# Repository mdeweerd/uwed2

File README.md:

# WARNING

Project not tested.

# INFORMATION

This is based on the open-source project "Open-Source Potentiostat
for Wireless Electrochemical Detection with Smartphones" 
=
See : https://dash.harvard.edu/bitstream/handle/1/37298552/5997382.pdf;jsessionid=20A09C47E57A66C76ECFA98192F31BF9?sequence=1

The reference to "UWED, Alar Ainla, GMW Group Harvard Univ" was left on the PCB.  They did not design this one, but it was adapted from their Eagle Project.

- The wireless module was replaced with an ESP-WROOM-32 because the original module is no longer supported.
- A programming connector was added.
- A THT connector has been added for power.
- A "Battery Management" IC was added to safely charge a Li-Ion/Li-Poly on power connector.
- There was a project to ajust the PAD positions to a Molex/1719730004

And some other "minor" changes as well as an effort to improve the ground plaine.

# SOFTWARE

See ac8b00850_si_002.zip from https://www.ncbi.nlm.nih.gov/pmc/articles/PMC5997382/ to get the original software as well as further information about this project.

The software has to be adapted to the ESP-WROOM-32.

# BUYING COMPONENTS

The original project ensured that all components were available from Digikey.

The `UWED2_proto.xls` file shows where these components were available in 2019.

At that time you would have been able to paste the following list on https://www.digikey.com/ordering/shoppingcart, but the BOM needs to be updated for some passive components and the ESP-WROOM-32 (was: 1904-1010-1-ND):
```csv
2,401-1427-1-ND,BOOT1;EN1
6,490-3340-2-ND,C1;C2;C5;C6;C16;C18
2,311-1136-1-ND,C10;C12
2,399-16641-1-ND,C20;C21
2,1276-1300-1-ND,C3;C4
9,478-1395-1-ND,C7-C9;C11;C13-C15;C17;C19
1,497-18870-1-ND,D7
1,1904-1010-1-ND,IC1
1,AD5667RBRMZ-2-ND,IC2
1,AD8608ARUZ-ND,IC3
2,576-1259-1-ND,IC4;IC5
1,MAX4643EUA+-ND,IC6
1,MAX4644EUT+TCT-ND,IC7
1,LTC2471IMS#PBF-ND,IC8
1,VAOL-S8SB4CT-ND,LED1
1,CP-032HPJCT-ND,P1
1,GH7540CT-ND,P2
1,RR12P1.2KDCT-ND,R1
2,541-4163-1-ND,R11;R12
2,A130132CT-ND,R14;R15
1,311-16.2KCRCT-ND,R2
2,311-845CRCT-ND,R3;R10
1,311-29.4KCRCT-ND,R4
1,311-8.06KCRCT-ND,R5
1,541-4126-1-ND,R7
3,541-4164-1-ND,R8;R9;R13
```

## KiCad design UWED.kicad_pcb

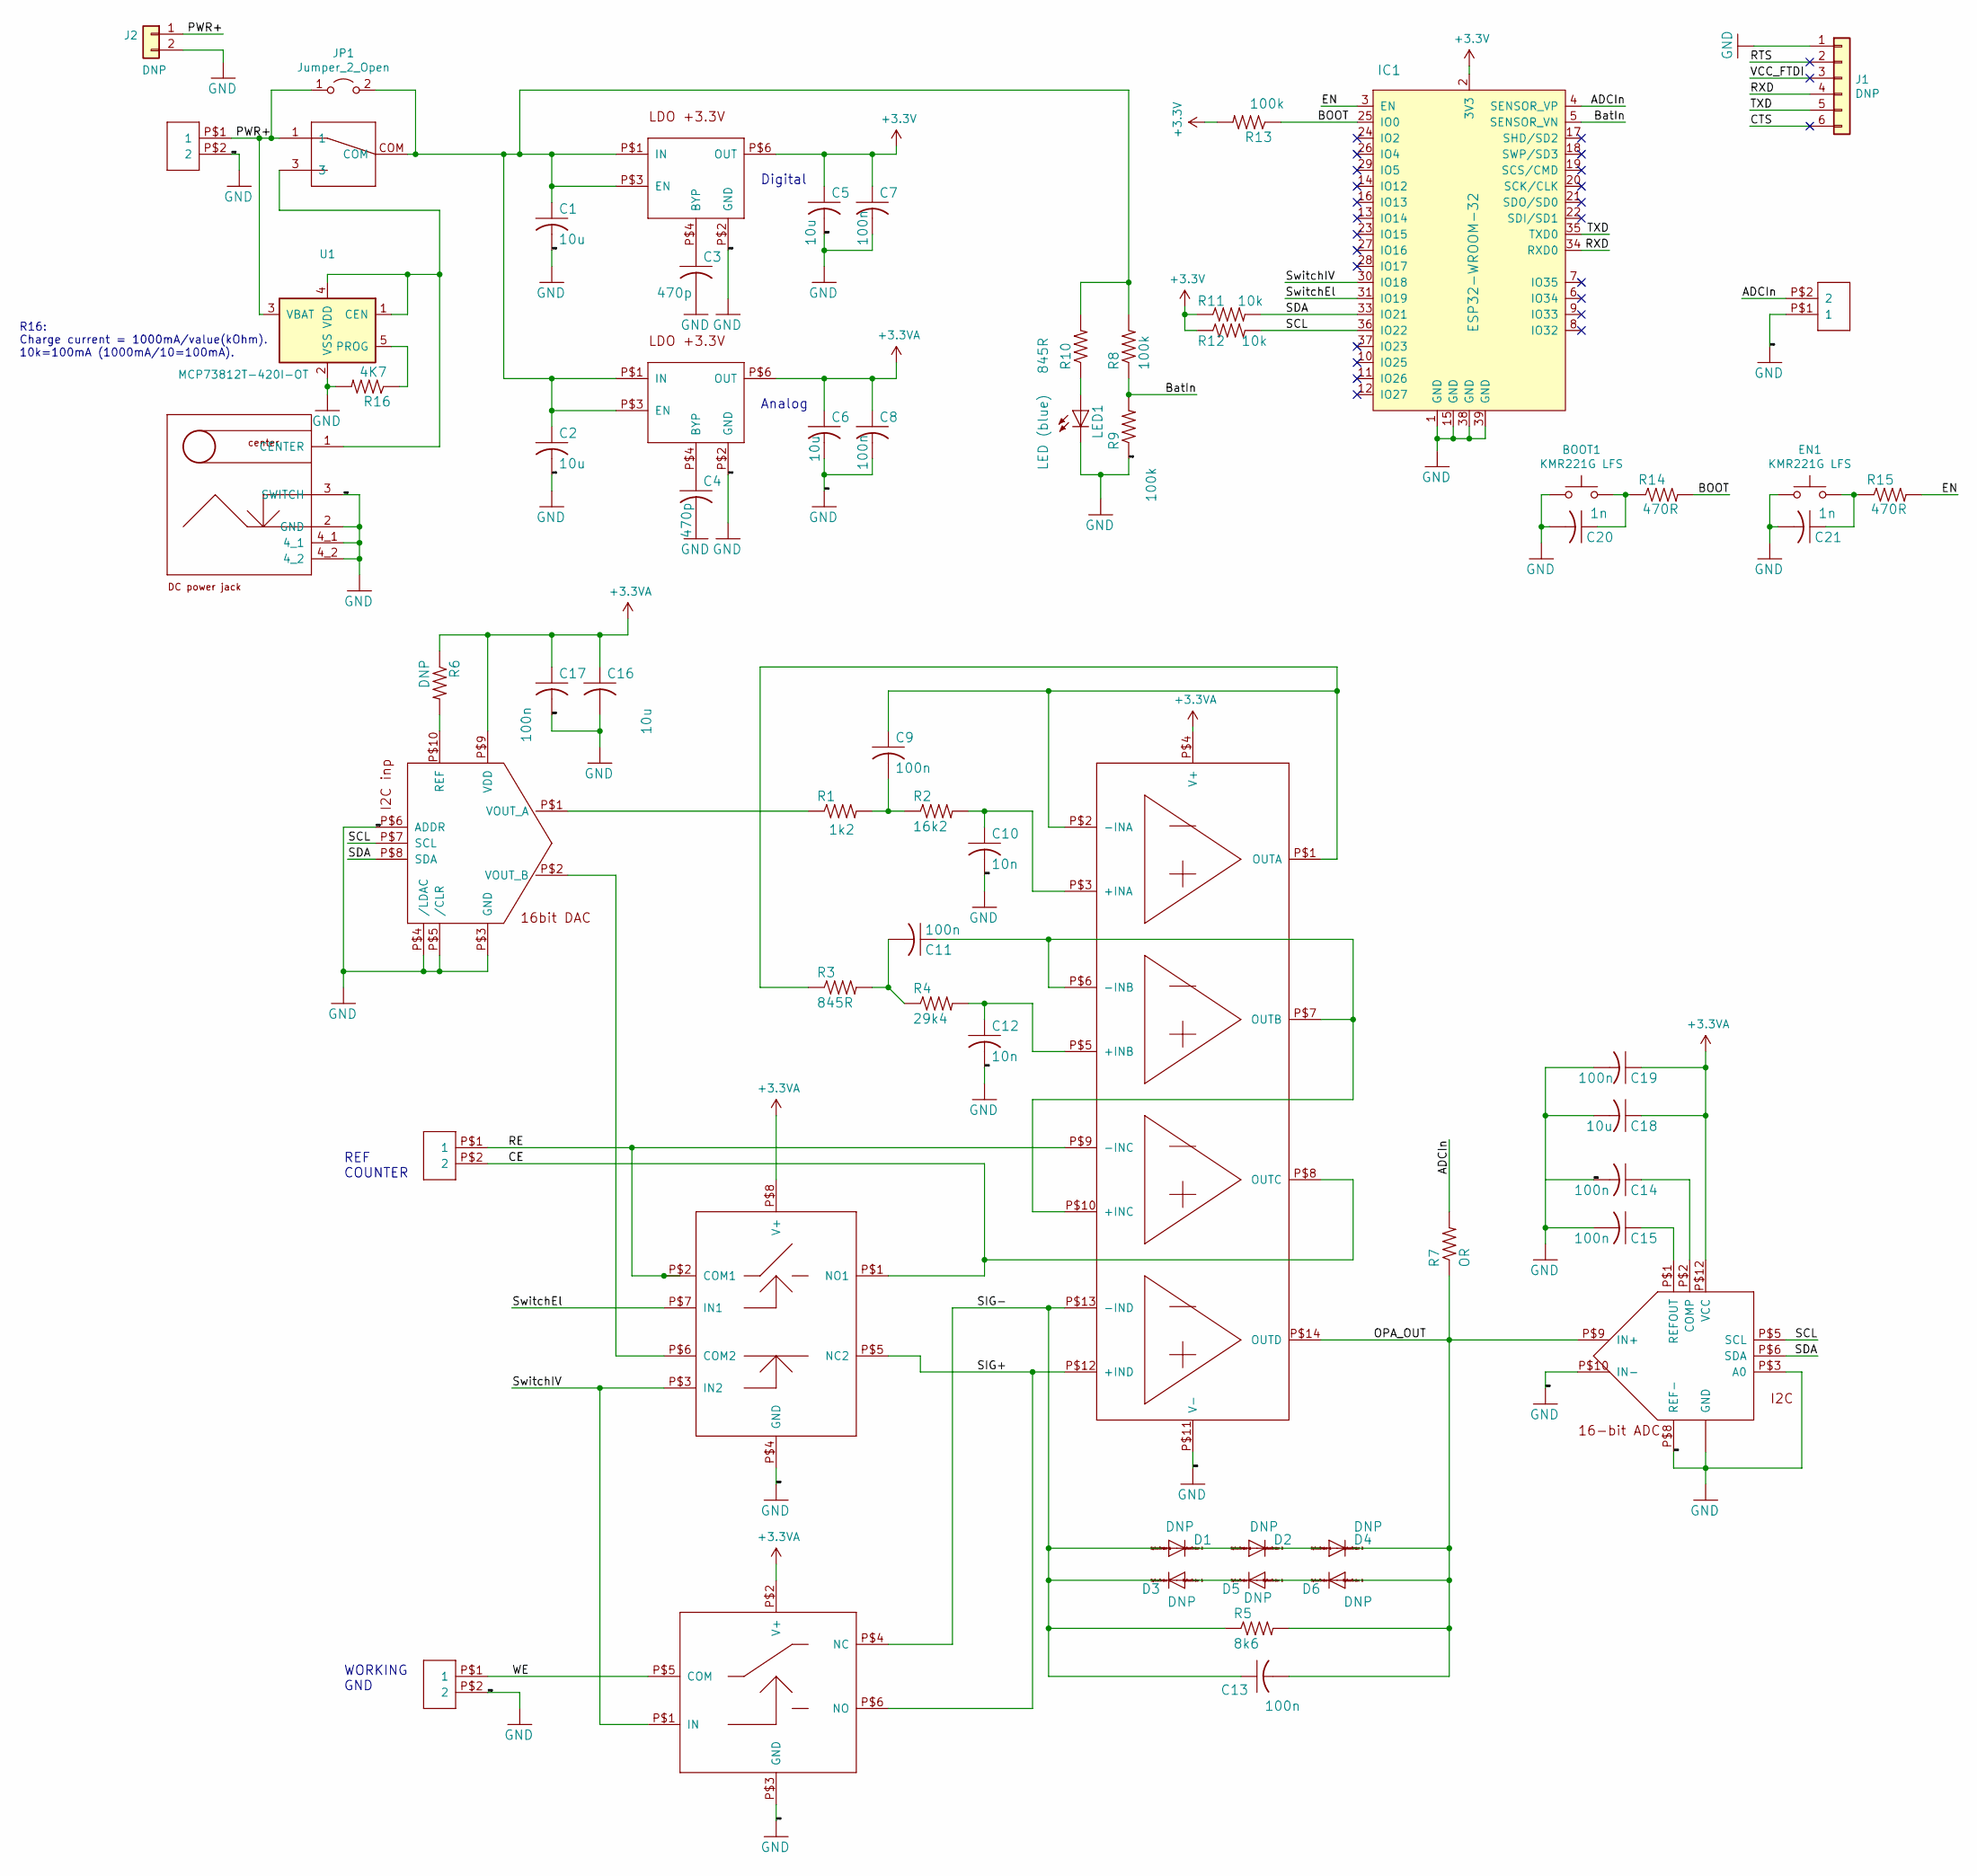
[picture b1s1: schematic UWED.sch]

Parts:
BOOT1: KMR221G LFS; SW_SPST_KMR2; mouser.manf# 611-KMR221G-LFS
C1, C2, C5, C6, C16, C18: 10u; C0805; digikey.manf# 490-3340-1-ND
C3, C4: 470p; C0805; digikey.manf# 1276-1300-1-ND
C7, C8, C9, C11, C13, C14, C15, C17, C19: 100n; C0805; digikey.manf# 478-1395-1-ND
C10, C12: 10n; C0805; digikey.manf# 311-1136-1-ND
C20, C21: 1n; C0805; digikey.manf# 399-16641-1-ND
D1, D2, D3, D4, D5, D6: DNP; SOD80C
EN1: KMR221G LFS; SW_SPST_KMR2; mouser.manf# 611-KMR221G-LFS
IC1: ESP32-WROOM-32; ESP32-WROOM-32D; MPN ESP32-WROOM-32; digikey.manf# 1904-1010-1-ND
IC2: DAC_AD5667RBRMZ-2; MSOP10_0.5MM; MPN AD5667RBRMZ-2; digikey.manf# AD5667RBRMZ-2-ND
IC3: 4OPAMPS-AD8608ARUZ; MSOP14_0.65MM; MPN AD8608ARUZ; digikey.manf# AD868ARUZ-ND
IC4, IC5: LDO-MIC5205-3.3YM5-TR; SOT-23-6; MPN MIC5205-3.3YM5-TR; digikey.manf# 576-1259-1-ND
IC6: SWITCH_MAX4643EUA; MSOP8_0.65MM; MPN MAX4643EUA+; digikey.manf# MAX4643EUA+-ND
IC7: SWITCH_MAX4644EUT; SOT-23-6; MPN MAX4644EUT+T; digikey.manf# MAX4644EUT+TCTND
IC8: ADC_LTC2471IMS; MSOP12_0.65MM; MPN LTC2471IMS#PBF; digikey.manf# LTC2471IMS#PBFND
J1: DNP; Pin_Header_Straight_1x06_Pitch2.54mm
J2: DNP; Pin_Header_Straight_1x02_Pitch2.54mm
JP1: Jumper_2_Open; SolderJumper-2_P1.3mm_Open_TrianglePad1.0x1.5mm
LED1: LED (blue); SML0805; digikey.manf# VAOL-S8SB4CT-ND
P1: PJ-032H-SMT-TR; PJ-032H-SMT; MPN PJ-032H-SMT-TR; digikey.manf# CP-032HPJCT-ND
P2: 34EWMSP12M6RT; TOGGLE_34E; MPN 34EWMSP12M6RT; digikey.manf# GH7540CT-ND
R1: 1k2; R0805; digikey.manf# RR12P1.2KDCT-ND
R2: 16k2; R0805; digikey.manf# 311-16.2KCRCT-ND
R3, R10: 845R; R0805; digikey.manf# 311-845CRCT-ND
R4: 29k4; R0805; digikey.manf# 311-29.4KCRCT-ND
R5: 8k6; R0805; digikey.manf# 311-8.06KCRCT-ND
R6: DNP; R0805; digikey.manf# 541-4126-1-ND
R7: OR; R0805; digikey.manf# 541-4126-1-ND
R8, R9, R13: 100k; R0805; digikey.manf# 541-4164-1-ND
R11, R12: 10k; R0805; digikey.manf# 541-4163-1-ND
R14, R15: 470R; R0805; digikey.manf# A130132CT-ND
R16: 4K7; R0805; digikey.manf# A130132CT-ND
U1: MCP73812T-420I-OT; SOT-23-5_HandSoldering
U$3, U$6, U$7, U$15: CONTACT_PADS_SMD_2

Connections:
+3.3VA: C6.1, C8.1, C16.1, C17.1, C18.1, C19.1, IC2.P$9 (VDD), IC3.P$4 (V+), IC5.P$6 (OUT), IC6.P$8 (V+), IC7.P$2 (V+), IC8.P$12 (VCC), R6.1
+3V3: C5.1, C7.1, IC1.2 (3V3), IC4.P$6 (OUT), R11.1, R12.1, R13.2
/ADCIn: IC1.4 (SENSOR_VP), R7.2, U$15.P$2 (2)
/BOOT: IC1.25 (IO0), R13.1, R14.2
/BatIn: IC1.5 (SENSOR_VN), R8.1, R9.2
/CE: IC3.P$8 (OUTC), IC6.P$1 (NO1), U$7.P$2 (2)
/CTS: J1.6
/EN: IC1.3 (EN), R15.2
/OPA_OUT: C13.2, D4.C, D6.A, IC3.P$14 (OUTD), IC8.P$9 (IN+), R5.2, R7.1
/PWR+: J2.1, JP1.1 (A), P2.1, U1.3 (VBAT), U$3.P$1 (1)
/RE: IC3.P$9 (-INC), IC6.P$2 (COM1), U$7.P$1 (1)
/RTS: J1.2
/RXD: IC1.34 (RXD0), J1.4
/SCL: IC1.36 (IO22), IC2.P$7 (SCL), IC8.P$5 (SCL), R12.2
/SDA: IC1.33 (IO21), IC2.P$8 (SDA), IC8.P$6 (SDA), R11.2
/SIG+: IC3.P$12 (+IND), IC6.P$5 (NC2), IC7.P$6 (NO)
/SIG-: C13.1, D1.A, D3.C, IC3.P$13 (-IND), IC7.P$4 (NC), R5.1
/SwitchEl: IC1.31 (IO19), IC6.P$7 (IN1)
/SwitchIV: IC1.30 (IO18), IC6.P$3 (IN2), IC7.P$1 (IN)
/TXD: IC1.35 (TXD0), J1.5
/VCC_FTDI: J1.3
/WE: IC7.P$5 (COM), U$6.P$1 (1)
GND: BOOT1.1, C1.2, C2.2, C3.2, C4.2, C5.2, C6.2, C7.2, C8.2, C10.2, C12.2, C14.2, C15.2, C16.2, C17.2, C18.2, C19.2, C20.2, C21.2, EN1.1, IC1.1 (GND), IC1.15 (GND), IC1.38 (GND), IC1.39 (GND), IC2.P$3 (GND), IC2.P$4 (/LDAC), IC2.P$5 (/CLR), IC2.P$6 (ADDR), IC3.P$11 (V-), IC4.P$2 (GND), IC5.P$2 (GND), IC6.P$4 (GND), IC7.P$3 (GND), IC8.P$3 (A0), IC8.P$4 (GND), IC8.P$7 (GND), IC8.P$8 (REF-), IC8.P$10 (IN-), IC8.P$11 (GND), J1.1, J2.2, LED1.C, P1.2 (GND), P1.3 (SWITCH), P1.4_1, P1.4_2, R9.1, R16.2, U1.2 (VSS), U$3.P$2 (2), U$6.P$2 (2), U$15.P$1 (1)
unnamed: BOOT1.2, C20.1, R14.1
unnamed: C1.1, C2.1, IC4.P$1 (IN), IC4.P$3 (EN), IC5.P$1 (IN), IC5.P$3 (EN), JP1.2 (B), P2.COM, R8.2, R10.2
unnamed: C3.1, IC4.P$4 (BYP)
unnamed: C4.1, IC5.P$4 (BYP)
unnamed: C9.1, IC3.P$1 (OUTA), IC3.P$2 (-INA), R3.1
unnamed: C9.2, R1.2, R2.1
unnamed: C10.1, IC3.P$3 (+INA), R2.2
unnamed: C11.1, IC3.P$6 (-INB), IC3.P$7 (OUTB), IC3.P$10 (+INC)
unnamed: C11.2, R3.2, R4.1
unnamed: C12.1, IC3.P$5 (+INB), R4.2
unnamed: C14.1, IC8.P$2 (COMP)
unnamed: C15.1, IC8.P$1 (REFOUT)
unnamed: C21.1, EN1.2, R15.1
unnamed: D1.C, D2.A
unnamed: D2.C, D4.A
unnamed: D3.A, D5.C
unnamed: D5.A, D6.C
unnamed: IC2.P$1 (VOUT_A), R1.1
unnamed: IC2.P$2 (VOUT_B), IC6.P$6 (COM2)
unnamed: IC2.P$10 (REF), R6.2
unnamed: LED1.A, R10.1
unnamed: P1.1 (CENTER), P2.3, U1.1 (CEN), U1.4 (VDD)
unnamed: R16.1, U1.5 (PROG)

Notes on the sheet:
Digital
Analog
REF COUNTER
WORKING GND
R16: Charge current = 1000mA/value(kOhm). 10k=100mA (1000mA/10=100mA).

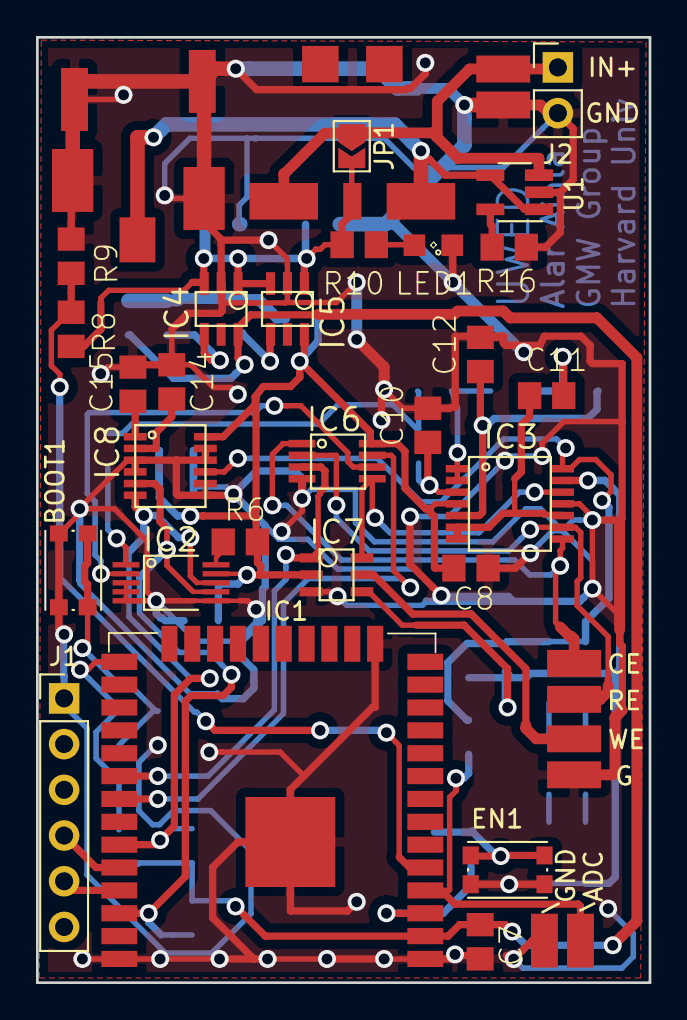
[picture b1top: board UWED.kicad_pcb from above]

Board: 2 copper layers, 34.0 x 52.5 mm, 64 parts (0 on the bottom side), 43 nets.

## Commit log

2019-07-04 New project files with ESP-WROOM-32 and integrated charger chip - untested.
2019-07-04 Add LICENSE
2021-04-06 Added README, filled in BOM to provide order list for DIGIKEY
2021-04-06 README update, kicost update
2021-04-06 Corrected readme for ESP-WROOM-32
2021-04-06 removed invalid comment
